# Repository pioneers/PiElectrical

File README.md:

# PiElectrical

This is the working repo for PiElectrical teams

1. [ToDo](#todo)
2. [Repo Structure](#repo-structure)
3. [Setup](#setup)
4. [Work Flow](#work-flow)
5. [How to Create a Gerber](#how-to-create-a-gerber)
6. [Docu Packets](#docu-packets)
7. [FAQ](#faq)
8. [Useful Links](#useful-links)
9. [Standards](#standards)

## ToDo:
* The stuff in PDB-Y16
* Convert motor controller design to KiCad
* Add and test current regulation for motor controller
* Talk to runtime and potentially use cheaper MCU for motor controller

[Back to Top](#pielectrical)

## Repo Structure:

**Boards**: Contains all necessary information about each board, including KiCad (and old Eagle) files, arduino test files, and board specific documentation.

**Bootloaders**: Contains the files necessary to burn the bootloader for boards identifying as Leonardo (Atmega32u4).

**Documentation**: All docu packets and scripts. *Fragile! Do not touch!*

**Production_Files**: Finalized gerbs and other necessary production files (BOM, CPL, etc...) sent out for fabrication.

**Images**: Place all your images in here to enhance your READMEs.

**Libraries**: Necessary KiCad files to work on PiElectrical

ToDo is on the README to keep things easier to see at first glance. GitHub issues tracker can be used as well.

[Back to Top](#pielectrical)

## Setup

<details>
    <summary>When you see an arrow like this... (click me)</summary>
        ...it indicates an expandable section. We usually include images in here as a better reference for you to follow along.
</details>

### Initial Setup of PiElectrical repo on your computer

1. Copy the URL for pioneers/PiElectrical to your clipboard: (Or here: https://github.com/pioneers/PiElectrical.git)
2. In Terminal (Mac, GNU/Linux) or Git Bash (windows), navigate to your working directory (the directory that you want to keep PiElectrical in.)
3. Clone PiElectrical by running this command: `git clone https://github.com/pioneers/PiElectrical.git`

### Installation of KiCad on your computer
1. Download the latest version of KiCad here: https://www.kicad.org/download/
2. <details>
    <summary>Run installer. Use all default settings on installer. (Click to see default settings)<br></summary>
    
</details>

### Setting up KiCad
1. Open KiCad.
2. <details>
    <summary>Depending on whether you've used KiCad before, select the appropriate option on the pop-up. (Default settings if you're new to KiCad).</summary>
    
   </details>

#### Adding Symbols
1. <details>
    <summary>Go to the <i>Preferences</i> tab, and select <i>Manage Symbol Libraries...</i></summary>
    
   </details>
2. <details>
    <summary>If this is your first time using KiCad, it will prompt you to configure the <i>Global Symbol Library</i>. It is highly recommended that you select "Copy default global symbol library table".</summary>
    
   </details>
3. <details>
    <summary>Select the folder icon near the bottom left and navigate to the <i>PiE_Symbols.kicad_sym</i> file in the <i>src</i> folder.</summary>
    
   </details>
4. <details>
    <summary>You should now see the <i>PiE_Symbols</i> in your Symbol Libraries. Make sure the "active" box is checked, and click "OK".</summary>
    
   </details>

#### Adding Footprints
1. <details>
    <summary>Go to the <i>Preferences</i> tab, and select <i>Manage Footprint Libraries...</i></summary>
    
   </details>
2. <details>
    <summary>If this is your first time using KiCad, it will prompt you to configure the <i>Global Footprint Library</i>. It is highly recommended that you select "Copy default global footprint library table".</summary>
    
   </details>
3. <details>
    <summary>Select the folder icon near the bottom left and navigate to the <i>PiE_Footprints.pretty</i> file in the <i>src</i> folder.</summary>
    
   </details>
4. <details>
    <summary>You should now see the <i>PiE_Footprints</i> in your Footprint Libraries. Make sure the "active" box is checked, and click "OK".</summary>
    
   </details>

Note that this setup instruction is based on KiCad 7.0.7, but it should still work for other versions.

[Back to Top](#pielectrical)

## Work Flow

Protocol when working on KiCad files

The revision number should be *REV \<year\>\<revision\>*. E.g. **REV 16A** for year 16 revision A.

If you are not quite familiar with git, see [Useful Links](#useful-links) for the PiE Github tutorial

**WARNING**: Do not modify PiE_Symbols.kicad_sym or PiE_Footprints.pretty without discussing it with PMs.

### Steps when working on KiCad files:

1. In Terminal (mac, GNU/Linux) or GitBash (windows), navigate to your working directory (wherever you have PiElectrical).
2. Make sure your working directory is clean: git status
3. If you haven't started your sub project: git checkout -b YOURNAME-SUBPROJECT
  3. YOUR\_NAME/SUBPROJECT is now the name of your branch
4. Do your work in KiCad.
5. Once you are at a good stopping point in your KiCad work, commit your progress:
    1. git add path/to/your/file
    2. git commit -m "Make your commit message short and with this format"
    3. **NOTE**: Commiting is like saving your file, but for all of PiE as well as your personal computer. And just like saving, Commit Early & Commit Often!
6. Repeat Steps 5 and 6 until you are finished with your EAGLE work.
7. Once you have made your last commit, push your files to the PiElectrical github repo: git push origin YOUR\_BRANCH
    - If you get a merge conflict, contact the PMs for help.
8. If **completely** done, submit a Pull Request

### Commit Message Format Conventions

* Present Tense ("Reroute power traces on team flag", not "Rerouted power traces on team flag")
* No period at the end: ("Reroute power traces on team flag", not "Reroute power traces on team flag.")
* Keep your message length to about one sentence.

### Merge Conflicts: What should I do?

Don't try to fix it yourself: Eagle files are finicky and you might break all your work!

Ask someone who knows how to deal with this, i.e. your PM or something

[Back to Top](#pielectrical)

## Generating Fabrication Outputs

1. Make sure you run the Electrical Rules Check (ERC) in the schematic and the Design Rules Checker (DRC) in the layout, and have no *red* errors. Feel free to ask PMs if you have any questions.
2. <details>
    <summary>Go to File -> Fabrication Outputs -> Gerbers (.gbr)...</summary>
    
   </details>
3. <details>
    <summary>If this is your first time using KiCad, it will prompt you to configure the <i>Global Symbol Library</i>. It is highly recommended that you select "Copy default global symbol library table".</summary>
    
   </details>
4. <details>
    <summary>Select the folder icon near the bottom left and navigate to the <i>PiE_Symbols.kicad_sym</i> file in the <i>src</i> folder.</summary>
    
   </details>
5. <details>
    <summary>You should now see the <i>PiE_Symbols</i> in your Symbol Libraries. Make sure the "active" box is checked, and click "OK".</summary>
    
   </details>

1. Open the brd file
2. Click Cam Job
3. Open pie.cam
4. Make a directory in each sensor's folder called SENSOR\_NAME-gerb
    * SENSOR\_NAME **must** be the exact name as the brd file
5. Run job, and click yes to all for the polygon issue
6. Once all the jobs are done, run `make gerb`

[Back to Top](#pielectrical)

## FAQ

Q: What's the difference between commit before I pull?

A: Do you want to keep any of the changes? Then commit those (the ones you want to keep) before you pull. Or else, the things you pull might conflict with your work, and you'll have a git disaster.

Q: I worked on my stuff, pulled, and everything I did went away!

A: As long as you committed, the PMs can recover your work for you.

Q: Why am I working on my own branch?

A: This is to keep track of pull request and board reviews on a per board basis

[Back to Top](#pielectrical)

## Useful Links

PiE's own [Github Tutorial](https://docs.google.com/a/pioneers.berkeley.edu/presentation/d/1ef5zSDMbE7dCu4XAC4dXhSV5iUd7gjCyXPjRrRvtbQI/edit?usp=sharing)

[PiElectrical Wiki](https://github.com/pioneers/PiElectrical/wiki)

[Markdown Cheatsheet](https://github.com/adam-p/markdown-here/wiki/Markdown-Cheatsheet)

[Arduino Pro Micro Pinouts](https://cdn.sparkfun.com/assets/9/c/3/c/4/523a1765757b7f5c6e8b4567.png)

[BAC DFM](http://instantdfm.bayareacircuits.com/)

Read up on the [PiE Electrical Style Rules and Guidelines](https://staff.pierobotics.org/wiki/Electrical_style_guidelines) (This is a good resource, but outdated)

[Back to Top](#pielectrical)

## Design Rules

You can find JLC's design rules here: https://jlcpcb.com/capabilities/pcb-capabilities. Please review this before ordering a PCB.

#### Some of our general rules:
- Traces **must** be multiples of 45 degrees
- Standard Pin Distance: 100 mils (2.54 mm)

#### Make sure to annotate your boards:

```
Copyright (c) 2023, Pioneers in Engineering
All rights reserved.

Design by: Justin H
This design is open source hardware.
For more information, visit 
github.com/pioneers/PiElectrical
```

[Back to Top](#pielectrical)

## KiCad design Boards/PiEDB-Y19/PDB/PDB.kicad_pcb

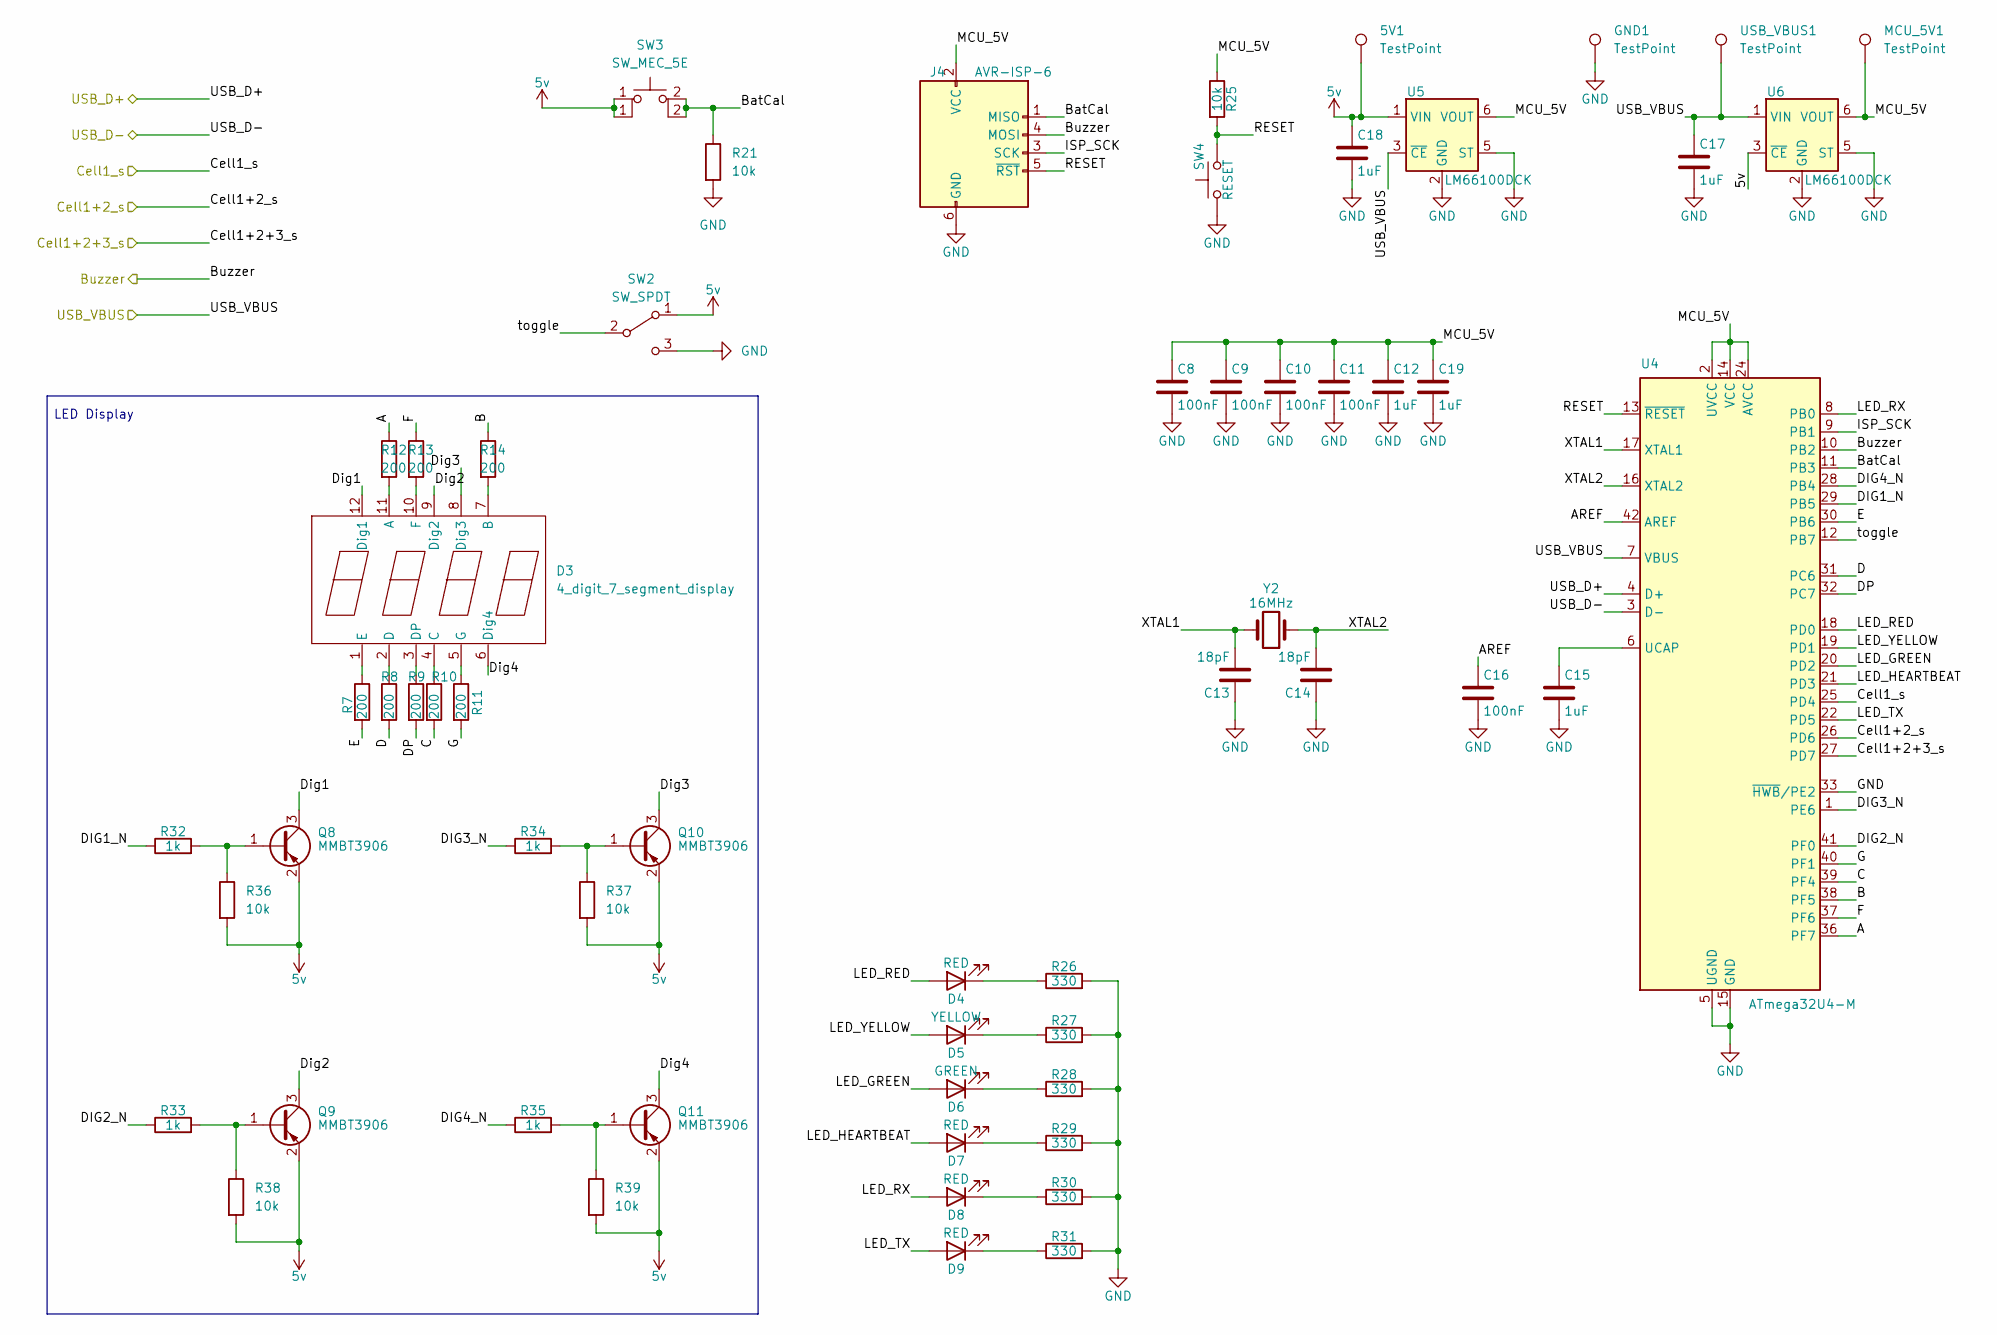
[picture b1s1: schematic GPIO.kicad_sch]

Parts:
5V1: TestPoint; TestPoint_Loop_D2.60mm_Drill0.9mm_Beaded
C8, C9, C10, C11, C16: 100nF; C_0603_1608Metric
C12, C15, C17, C18, C19: 1uF; C_0603_1608Metric
C13, C14: 18pF; C_0603_1608Metric
D3: 4_digit_7_segment_display; LED-SEG-TH_12P-L30.0-W13.7-P2.54-S10.16-BL
D4, D7, D8, D9: RED; LED_0805_2012Metric
D5: YELLOW; LED_0805_2012Metric
D6: GREEN; LED_0805_2012Metric
GND1: TestPoint; TestPoint_Loop_D2.60mm_Drill0.9mm_Beaded
J4: AVR-ISP-6; PinHeader_2x03_P2.54mm_Vertical
MCU_5V1: TestPoint; TestPoint_Loop_D2.60mm_Drill0.9mm_Beaded
Q8, Q9, Q10, Q11: MMBT3906; SOT-23
R7, R8, R9, R10, R11, R12, R13, R14: 200; R_0603_1608Metric
R21, R36, R37, R38, R39: 10k; R_0402_1005Metric
R25: 10k; R_0603_1608Metric
R26, R27, R28, R29, R30, R31: 330; R_0603_1608Metric
R32, R33, R34, R35: 1k; R_0603_1608Metric
SW2: SW_SPDT; DEALON SS-12D01-G3
SW3: SW_MEC_5E; SW_PUSH_6mm
SW4: RESET; SW_PUSH_6mm
U4: ATmega32U4-M; QFN-44-1EP_7x7mm_P0.5mm_EP5.2x5.2mm
U5, U6: LM66100DCK; SOT-363_SC-70-6
USB_VBUS1: TestPoint; TestPoint_Loop_D2.60mm_Drill0.9mm_Beaded
Y2: 16MHz; Crystal_SMD_5032-2Pin_5.0x3.2mm

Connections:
5v: 5V1.1 (1_1), C18.1, Q8.2 (E), Q9.2 (E), Q10.2 (E), Q11.2 (E), R36.2, R37.2, R38.2, R39.2, SW2.1 (A), SW3.1, U5.1 (VIN), U6.3 (~CE); also elsewhere on the board
/Buzzer: J4.4 (MOSI), U4.10 (PB2); also elsewhere on the board
/Cell1+2+3_s: U4.27 (PD7); also elsewhere on the board
/Cell1+2_s: U4.26 (PD6); also elsewhere on the board
/Cell1_s: U4.25 (PD4); also elsewhere on the board
/GPIO/A: R12.1, U4.36 (PF7)
/GPIO/AREF: C16.1, U4.42 (AREF)
/GPIO/B: R14.1, U4.38 (PF5)
/GPIO/BatCal: J4.1 (MISO), R21.1, SW3.2 (A), U4.11 (PB3)
/GPIO/C: R10.2, U4.39 (PF4)
/GPIO/D: R8.2, U4.31 (PC6)
/GPIO/DIG1_N: R32.1, U4.29 (PB5)
/GPIO/DIG2_N: R33.1, U4.41 (PF0)
/GPIO/DIG3_N: R34.1, U4.1 (PE6)
/GPIO/DIG4_N: R35.1, U4.28 (PB4)
/GPIO/DP: R9.2, U4.32 (PC7)
/GPIO/Dig1: D3.12 (Dig1), Q8.3 (C)
/GPIO/Dig2: D3.9 (Dig2), Q9.3 (C)
/GPIO/Dig3: D3.8 (Dig3), Q10.3 (C)
/GPIO/Dig4: D3.6 (Dig4), Q11.3 (C)
/GPIO/E: R7.2, U4.30 (PB6)
/GPIO/F: R13.1, U4.37 (PF6)
/GPIO/G: R11.2, U4.40 (PF1)
/GPIO/ISP_SCK: J4.3 (SCK), U4.9 (PB1)
/GPIO/LED_GREEN: D6.2 (A), U4.20 (PD2)
/GPIO/LED_HEARTBEAT: D7.2 (A), U4.21 (PD3)
/GPIO/LED_RED: D4.2 (A), U4.18 (PD0)
/GPIO/LED_RX: D8.2 (A), U4.8 (PB0)
/GPIO/LED_TX: D9.2 (A), U4.22 (PD5)
/GPIO/LED_YELLOW: D5.2 (A), U4.19 (PD1)
/GPIO/MCU_5V: C8.1, C9.1, C10.1, C11.1, C12.1, C19.1, J4.2 (VCC), MCU_5V1.1 (1_1), R25.1, U4.2 (UVCC), U4.14 (VCC), U4.24 (AVCC), U4.34 (VCC), U4.44 (AVCC), U5.6 (VOUT), U6.6 (VOUT)
/GPIO/RESET: J4.5 (~RST), R25.2, SW4.2, U4.13 (~RESET)
/GPIO/USB_D+: U4.4 (D+); also elsewhere on the board
/GPIO/USB_D-: U4.3 (D-); also elsewhere on the board
/GPIO/USB_VBUS: C17.1, U4.7 (VBUS), U5.3 (~CE), U6.1 (VIN), USB_VBUS1.1 (1_1); also elsewhere on the board
/GPIO/XTAL1: C13.2, U4.17 (XTAL1), Y2.2
/GPIO/XTAL2: C14.2, U4.16 (XTAL2), Y2.1
/GPIO/toggle: SW2.2 (B), U4.12 (PB7)
GND: C8.2, C9.2, C10.2, C11.2, C12.2, C13.1, C14.1, C15.2, C16.2, C17.2, C18.2, C19.2, GND1.1 (1_1), J4.6 (GND), R21.2, R26.2, R27.2, R28.2, R29.2, R30.2, R31.2, SW2.3 (C), SW4.1, U4.5 (UGND), U4.15 (GND), U4.23 (GND), U4.33 (~HWB/PE2), U4.35 (GND), U4.43 (GND), U4.45 (GND), U5.2 (GND), U5.5 (ST), U6.2 (GND), U6.5 (ST); also elsewhere on the board
unnamed: D3.11 (A), R12.2
unnamed: D3.7 (B), R14.2
unnamed: D3.4 (C), R10.1
unnamed: D3.2 (D), R8.1
unnamed: D3.3 (DP), R9.1
unnamed: D3.1 (E), R7.1
unnamed: D3.10 (F), R13.2
unnamed: D3.5 (G), R11.1
unnamed: D4.1 (K), R26.1
unnamed: D5.1 (K), R27.1
unnamed: D6.1 (K), R28.1
unnamed: D7.1 (K), R29.1
unnamed: D8.1 (K), R30.1
unnamed: D9.1 (K), R31.1
unnamed: Q8.1 (B), R32.2, R36.1
unnamed: Q9.1 (B), R33.2, R38.1
unnamed: Q10.1 (B), R34.2, R37.1
unnamed: Q11.1 (B), R35.2, R39.1
unnamed: C15.1, U4.6 (UCAP)

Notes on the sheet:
LED Display

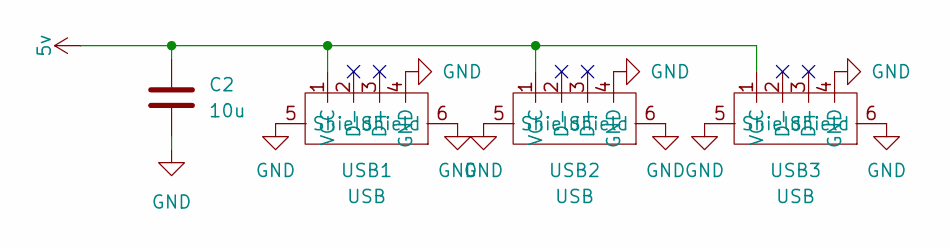
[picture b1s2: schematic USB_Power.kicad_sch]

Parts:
C2: 10u; CP_Radial_D5.0mm_P2.00mm
USB1, USB2, USB3: USB; USB-A_female

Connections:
5v: C2.1, USB1.1 (VCC), USB2.1 (VCC), USB3.1 (VCC); also elsewhere on the board
GND: C2.2, USB1.4 (GND), USB1.5 (Shield), USB1.6 (Shield), USB2.4 (GND), USB2.5 (Shield), USB2.6 (Shield), USB3.4 (GND), USB3.5 (Shield), USB3.6 (Shield); also elsewhere on the board

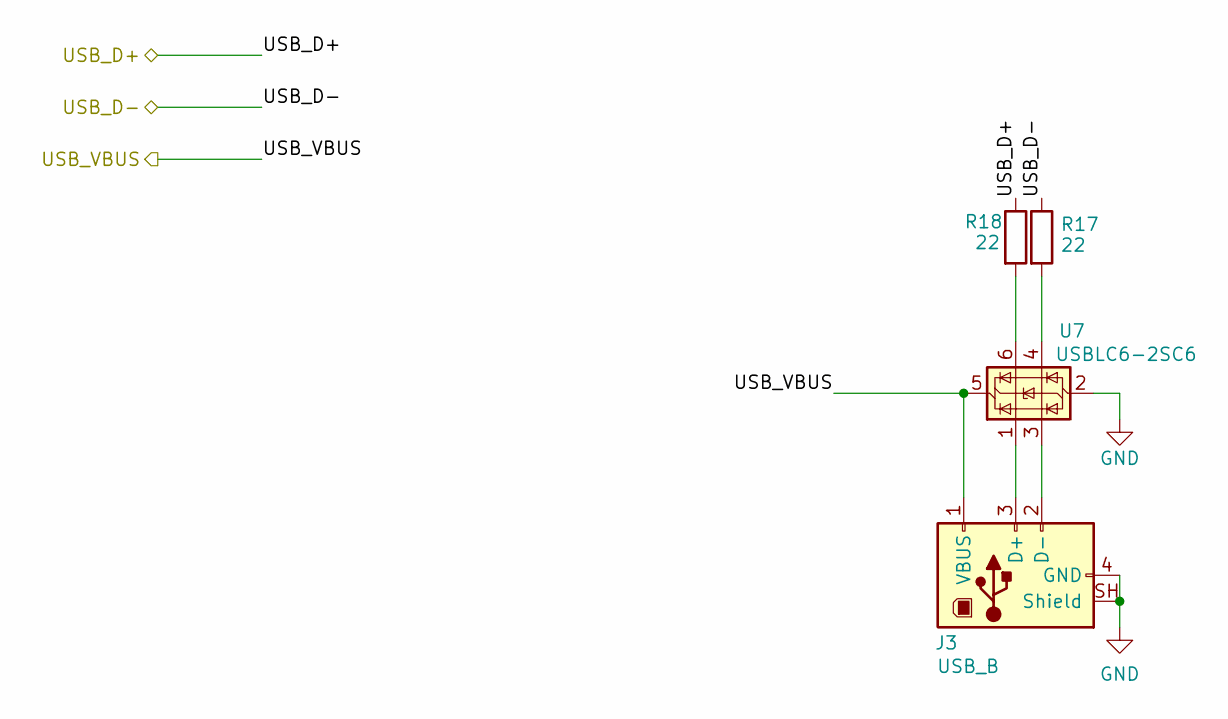
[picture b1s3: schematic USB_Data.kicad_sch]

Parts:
J3: USB_B; USB_B_OST_USB-B1HSxx_Horizontal
R17, R18: 22; R_0603_1608Metric
U7: USBLC6-2SC6; SOT-23-6

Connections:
/GPIO/USB_D+: R18.1; also elsewhere on the board
/GPIO/USB_D-: R17.1; also elsewhere on the board
/GPIO/USB_VBUS: J3.1 (VBUS), U7.5 (VBUS); also elsewhere on the board
GND: J3.4 (GND), J3.SH (Shield), U7.2 (GND); also elsewhere on the board
unnamed: J3.3 (D+), U7.1 (I/O1)
unnamed: J3.2 (D-), U7.3 (I/O2)
unnamed: R17.2, U7.4 (I/O2)
unnamed: R18.2, U7.6 (I/O1)

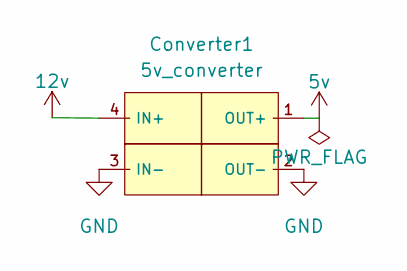
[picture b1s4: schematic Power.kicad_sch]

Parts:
Converter1: 5v_converter

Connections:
5v: Converter1.1 (OUT+); also elsewhere on the board
12v: Converter1.4 (IN+); also elsewhere on the board
GND: Converter1.2 (OUT-), Converter1.3 (IN-); also elsewhere on the board

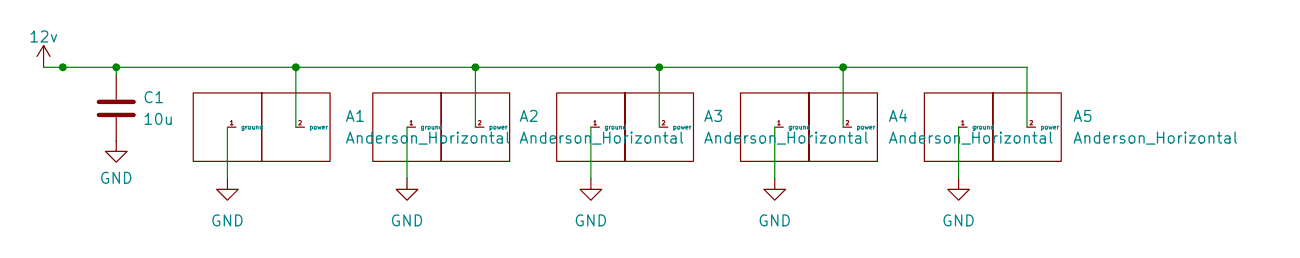
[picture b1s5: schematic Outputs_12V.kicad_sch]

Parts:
A1, A2, A3, A4, A5: Anderson_Horizontal; anderson_horizontal
C1: 10u; CP_Radial_D5.0mm_P2.00mm

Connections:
12v: A1.2 (power), A2.2 (power), A3.2 (power), A4.2 (power), A5.2 (power), C1.1; also elsewhere on the board
GND: A1.1 (ground), A2.1 (ground), A3.1 (ground), A4.1 (ground), A5.1 (ground), C1.2; also elsewhere on the board

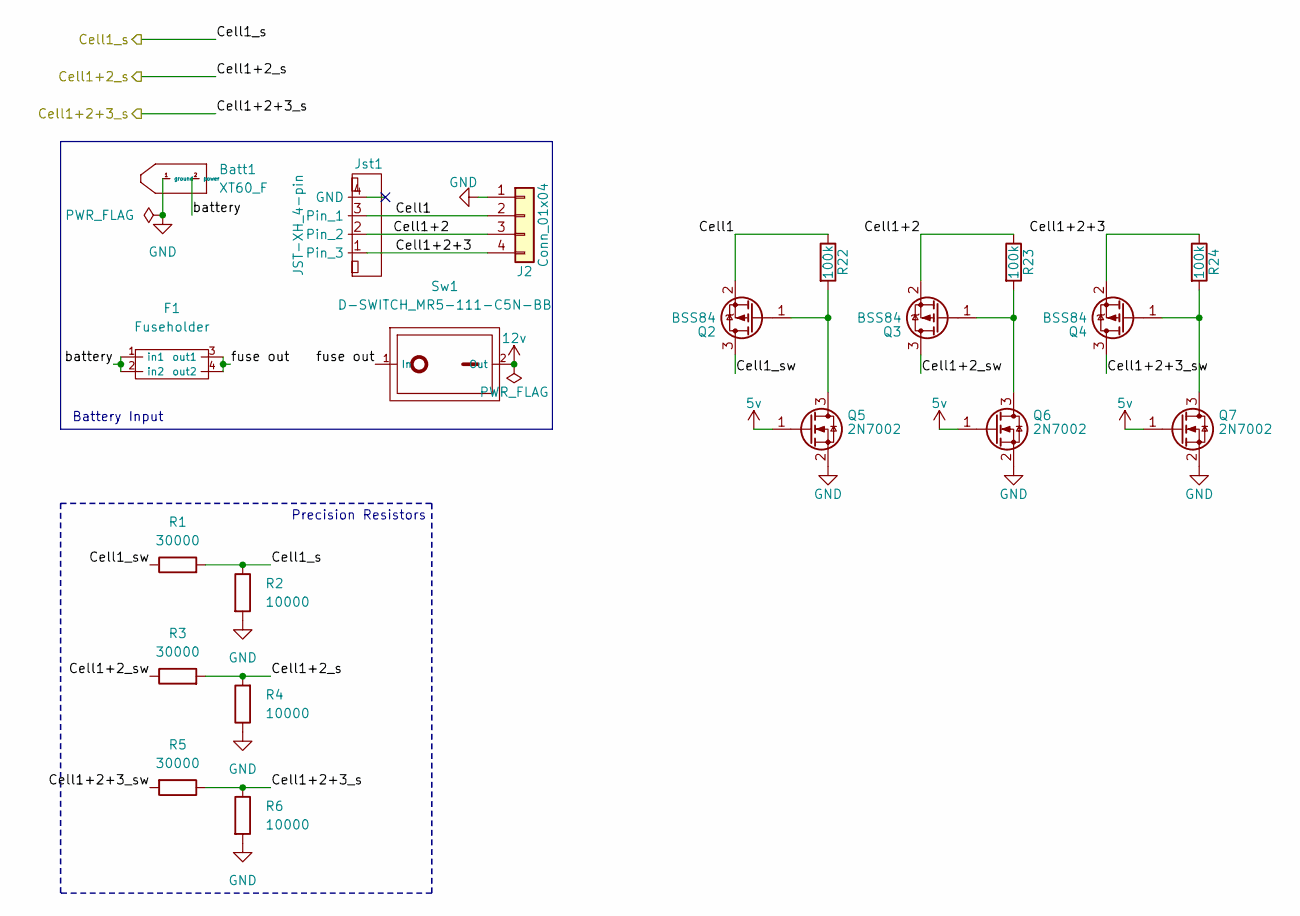
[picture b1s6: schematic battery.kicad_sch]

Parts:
Batt1: XT60_F; AMASS_XT60-M_1x02_P7.20mm_Vertical
F1: Fuseholder; Fuse Holder SMD
J2: Conn_01x04; PinHeader_1x04_P2.54mm_Vertical
Jst1: JST-XH_4-pin; JST_XH_B4B-XH-A_1x04_P2.50mm_Vertical
Q2, Q3, Q4: BSS84; SOT-23
Q5, Q6, Q7: 2N7002; SOT-23
R1, R3, R5: 30000; R_0603_1608Metric
R2, R4, R6: 10000; R_0603_1608Metric
R22, R23, R24: 100k; R_0603_1608Metric
Sw1: D-SWITCH_MR5-111-C5N-BB; Rocker Switch

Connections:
5v: Q5.1 (G), Q6.1 (G), Q7.1 (G); also elsewhere on the board
12v: Sw1.2 (Out); also elsewhere on the board
/Battery/Cell1: J2.2, Jst1.3 (Pin_1), Q2.2 (S), R22.1
/Battery/Cell1+2: J2.3, Jst1.2, Q3.2 (S), R23.1
/Battery/Cell1+2+3: J2.4, Jst1.1 (Pin_3), Q4.2 (S), R24.1
/Battery/Cell1+2+3_sw: Q4.3 (D), R5.2
/Battery/Cell1+2_sw: Q3.3 (D), R3.1
/Battery/Cell1_sw: Q2.3 (D), R1.1
/Battery/battery: Batt1.2 (power), F1.1 (in1), F1.2 (in2)
/Battery/fuse out: F1.3 (out1), F1.4 (out2), Sw1.1 (In)
/Cell1+2+3_s: R5.1, R6.1; also elsewhere on the board
/Cell1+2_s: R3.2, R4.2; also elsewhere on the board
/Cell1_s: R1.2, R2.1; also elsewhere on the board
GND: Batt1.1 (ground), J2.1, Q5.2 (S), Q6.2 (S), Q7.2 (S), R2.2, R4.1, R6.2; also elsewhere on the board
unnamed: Q2.1 (G), Q5.3 (D), R22.2
unnamed: Q3.1 (G), Q6.3 (D), R23.2
unnamed: Q4.1 (G), Q7.3 (D), R24.2

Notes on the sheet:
Precision Resistors
Battery Input

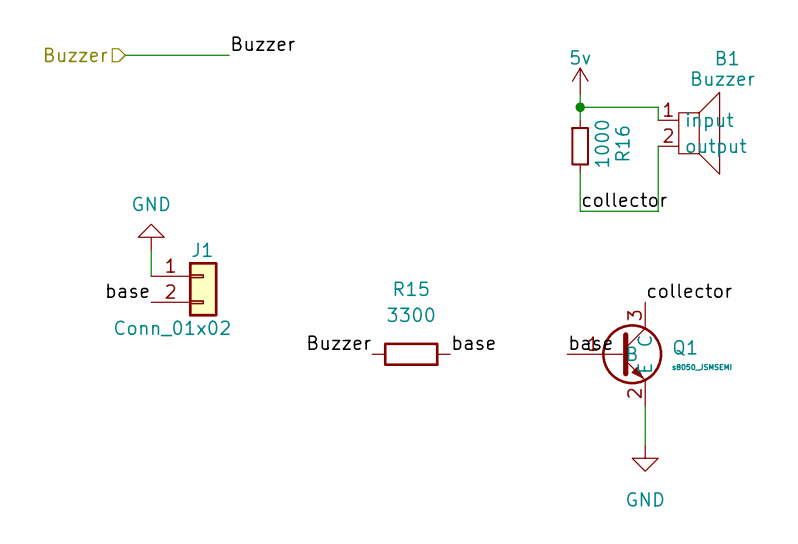
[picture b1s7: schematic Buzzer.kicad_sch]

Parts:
B1: Buzzer
J1: Conn_01x02; PinHeader_1x02_P2.54mm_Vertical
Q1: s8050_JSMSEMI; s8050 JSMSEMI
R15: 3300; R_0603_1608Metric
R16: 1000; R_0603_1608Metric

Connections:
5v: B1.1 (input), R16.1; also elsewhere on the board
/Buzzer: R15.1; also elsewhere on the board
/Buzzer/base: J1.2, Q1.1 (B), R15.2
/Buzzer/collector: B1.2 (output), Q1.3 (C), R16.2
GND: J1.1, Q1.2 (E); also elsewhere on the board

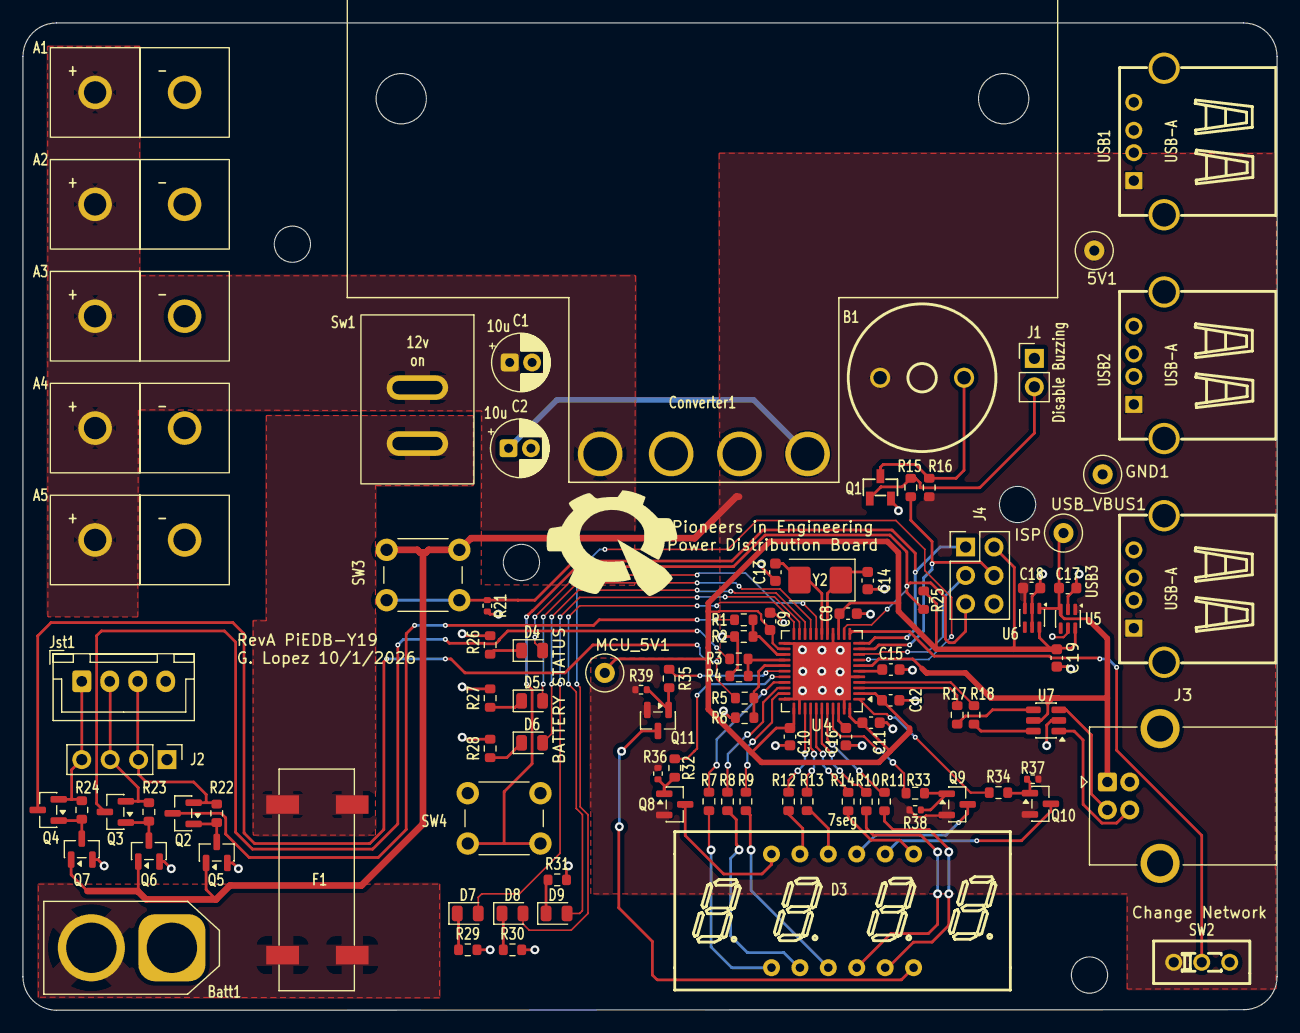
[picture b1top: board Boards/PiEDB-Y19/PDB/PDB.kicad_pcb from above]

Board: 2 copper layers, 112.1 x 88.2 mm, 99 parts (0 on the bottom side), 76 nets.

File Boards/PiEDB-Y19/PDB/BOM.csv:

"Id";"Designator";"Footprint";"Quantity";"Designation";"Supplier and ref";
1;"5V1, GND1, MCU_5V1, USB_VBUS1";"TestPoint_Loop_D2.60mm_Drill0.9mm_Beaded";4;"TestPoint";;;
2;"A1, A2, A3, A4, A5";"anderson_horizontal";5;"Anderson_Horizontal";;;
3;"B1";"Buzzer";1;"Buzzer";;;
4;"Batt1";"AMASS_XT60-M_1x02_P7.20mm_Vertical";1;"XT60_F";;;
5;"C1, C2";"CP_Radial_D5.0mm_P2.00mm";2;"10u";;;
6;"C8, C9, C10, C11, C16";"C_0603_1608Metric";5;"100nF";;;
7;"C12, C15, C17, C18, C19";"C_0603_1608Metric";5;"1uF";;;
8;"C13, C14";"C_0603_1608Metric";2;"18pF";;;
9;"Converter1";"5v_converter";1;"5v_converter";;;
10;"D3";"LED-SEG-TH_12P-L30.0-W13.7-P2.54-S10.16-BL";1;"4_digit_7_segment_display";;;
11;"D4, D7, D8, D9";"LED_0805_2012Metric";4;"RED";;;
12;"D5";"LED_0805_2012Metric";1;"YELLOW";;;
13;"D6";"LED_0805_2012Metric";1;"GREEN";;;
14;"F1";"Fuse Holder SMD";1;"Fuseholder";;;
15;"J1";"PinHeader_1x02_P2.54mm_Vertical";1;"Conn_01x02";;;
16;"J2";"PinHeader_1x04_P2.54mm_Vertical";1;"Conn_01x04";;;
17;"J3";"USB_B_OST_USB-B1HSxx_Horizontal";1;"USB_B";;;
18;"J4";"PinHeader_2x03_P2.54mm_Vertical";1;"AVR-ISP-6";;;
19;"Jst1";"JST_XH_B4B-XH-A_1x04_P2.50mm_Vertical";1;"JST-XH_4-pin";;;
20;"Q1";"s8050 JSMSEMI";1;"s8050_JSMSEMI";;;
21;"Q2, Q3, Q4";"SOT-23";3;"BSS84";;;
22;"Q5, Q6, Q7";"SOT-23";3;"2N7002";;;
23;"Q8, Q9, Q10, Q11";"SOT-23";4;"MMBT3906";;;
24;"R1, R3, R5";"R_0603_1608Metric";3;"30000";;;
25;"R2, R4, R6";"R_0603_1608Metric";3;"10000";;;
26;"R7, R8, R9, R10, R11, R12, R13, R14";"R_0603_1608Metric";8;"200";;;
27;"R15";"R_0603_1608Metric";1;"3300";;;
28;"R16";"R_0603_1608Metric";1;"1000";;;
29;"R17, R18";"R_0603_1608Metric";2;"22";;;
30;"R21, R36, R37, R38, R39";"R_0402_1005Metric";5;"10k";;;
31;"R22, R23, R24";"R_0603_1608Metric";3;"100k";;;
32;"R25";"R_0603_1608Metric";1;"10k";;;
33;"R26, R27, R28, R29, R30, R31";"R_0603_1608Metric";6;"330";;;
34;"R32, R33, R34, R35";"R_0603_1608Metric";4;"1k";;;
35;"REF**, REF**, REF**, REF**";"Hole_R1.62mm";4;"Hole_R1.62mm";;;
36;"Sw1";"Rocker Switch";1;"D-SWITCH_MR5-111-C5N-BB";;;
37;"SW2";"DEALON SS-12D01-G3";1;"SW_SPDT";;;
38;"SW3";"SW_PUSH_6mm";1;"SW_MEC_5E";;;
39;"SW4";"SW_PUSH_6mm";1;"RESET";;;
40;"U4";"QFN-44-1EP_7x7mm_P0.5mm_EP5.2x5.2mm";1;"ATmega32U4-M";;;
41;"U5, U6";"SOT-363_SC-70-6";2;"LM66100DCK";;;
42;"U7";"SOT-23-6";1;"USBLC6-2SC6";;;
43;"USB1, USB2, USB3";"USB-A_female";3;"USB";;;
44;"Y2";"Crystal_SMD_5032-2Pin_5.0x3.2mm";1;"16MHz";;;

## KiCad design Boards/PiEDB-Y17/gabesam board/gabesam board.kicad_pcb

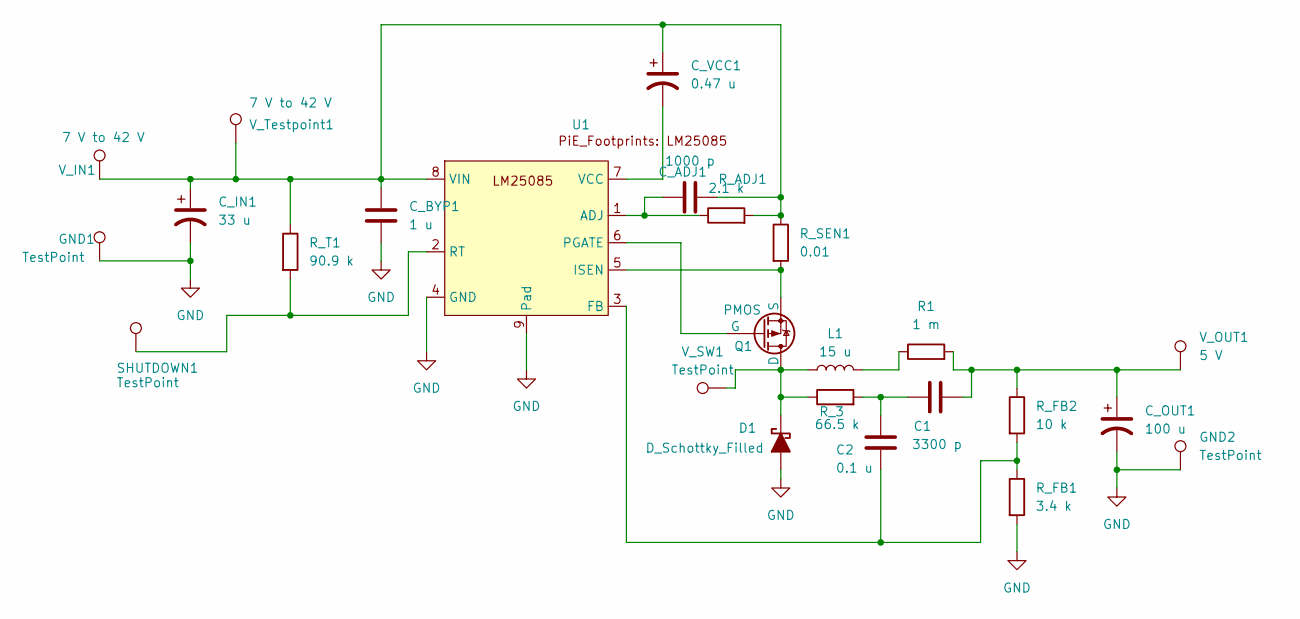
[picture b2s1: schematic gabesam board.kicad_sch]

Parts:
C1: 3300 p; C_1206
C2: 0.1 u; C_1206
C_ADJ1: 1000 p; C_1206
C_BYP1: 1 u; C_1206
C_IN1: 33 u; C_1206
C_OUT1: 100 u; C_1206
C_VCC1: 0.47 u; C_1206
D1: D_Schottky_Filled; D_1206_3216Metric_Pad1.42x1.75mm_HandSolder
GND1, GND2: TestPoint; TestPoint_Loop_D2.60mm_Drill0.9mm_Beaded
L1: 15 u; L_1206_3216Metric
Q1: PMOS; PowerPAK_SO-8_Single
R1: 1 m; R_1206
R_3: 66.5 k; R_1206
R_ADJ1: 2.1 k; R_1206
R_FB1: 3.4 k; R_1206
R_FB2: 10 k; R_1206
R_SEN1: 0.01; R_1206
R_T1: 90.9 k; R_1206
SHUTDOWN1: TestPoint; TestPoint_Loop_D2.60mm_Drill0.9mm_Beaded
U1: LM25085-Q1
V_IN1: 7 V to 42 V; TestPoint_Loop_D2.60mm_Drill0.9mm_Beaded
V_OUT1: 5 V; TestPoint_Loop_D2.60mm_Drill0.9mm_Beaded
V_SW1: TestPoint; TestPoint_Loop_D2.60mm_Drill0.9mm_Beaded
V_Testpoint1: 7 V to 42 V; TestPoint_Loop_D2.60mm_Drill0.9mm_Beaded

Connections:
GND: C_BYP1.2, C_IN1.2, C_OUT1.2, D1.2 (A), GND1.1, GND2.1, R_FB1.2, U1.4 (GND), U1.9 (Pad)
unnamed: C1.1, C2.2, R_3.2
unnamed: C1.2, C_OUT1.1, R1.2, R_FB2.1, V_OUT1.1
unnamed: D1.1 (K), L1.1, Q1.1 (D), R_3.1, V_SW1.1
unnamed: L1.2, R1.1
unnamed: Q1.2 (G), U1.6 (PGATE)
unnamed: Q1.3 (S), R_SEN1.2, U1.5 (ISEN)
unnamed: C_ADJ1.1, R_ADJ1.1, U1.1 (ADJ)
unnamed: C2.1, R_FB1.1, R_FB2.2, U1.3 (FB)
unnamed: R_T1.2, SHUTDOWN1.1, U1.2 (RT)
unnamed: C_VCC1.2, U1.7 (VCC)
unnamed: C_ADJ1.2, C_BYP1.1, C_IN1.1, C_VCC1.1, R_ADJ1.2, R_SEN1.1, R_T1.1, U1.8 (VIN), V_IN1.1, V_Testpoint1.1

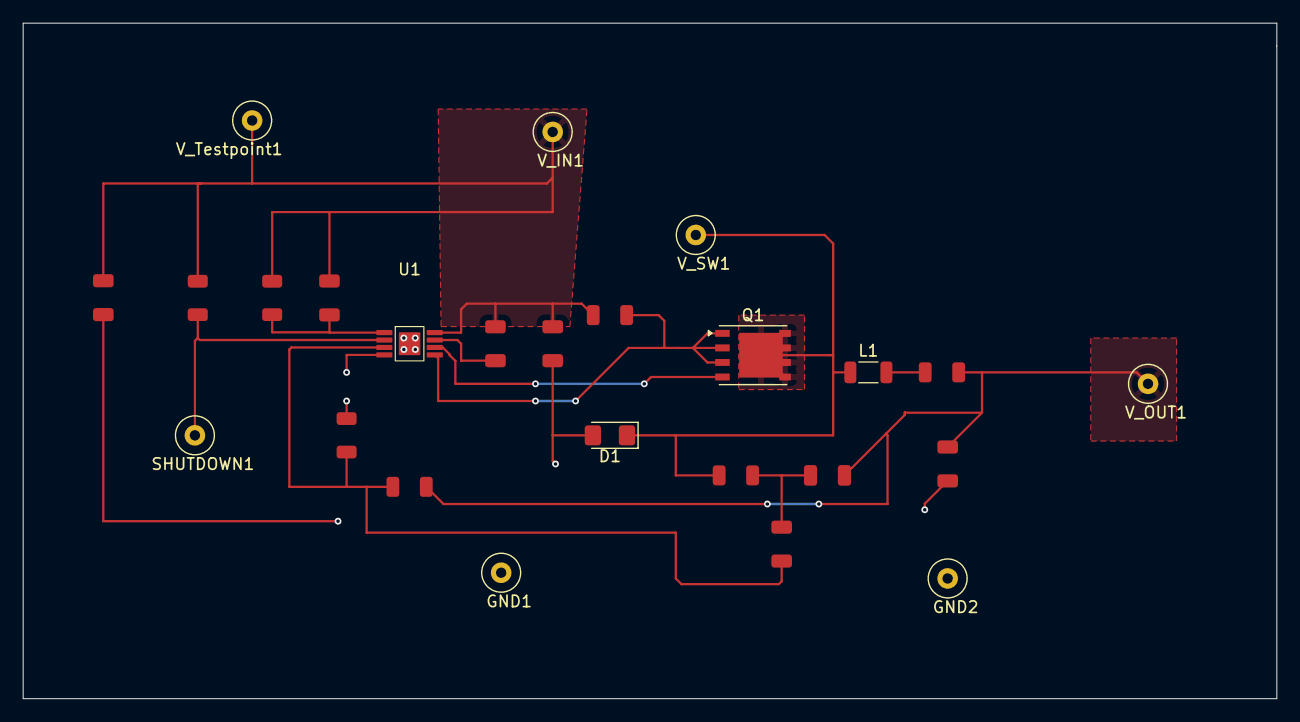
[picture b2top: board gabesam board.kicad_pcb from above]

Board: 2 copper layers, 109.5 x 59.0 mm, 25 parts (0 on the bottom side), 12 nets.

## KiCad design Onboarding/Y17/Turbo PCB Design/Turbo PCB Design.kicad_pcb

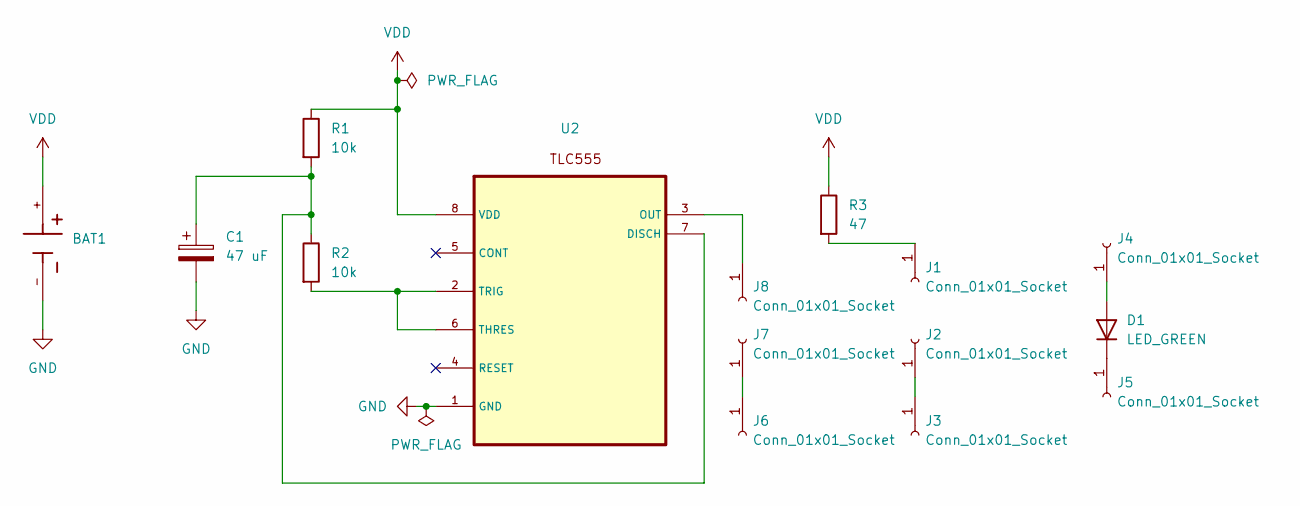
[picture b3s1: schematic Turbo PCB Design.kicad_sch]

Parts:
BAT1: BAT_BS-7
C1: 47 uF; CP_Radial_D4.0mm_P1.50mm
D1: LED_GREEN; LED_D5.0mm
J1, J2, J3, J4, J5, J6, J7, J8: Conn_01x01_Socket; MountingHole_1.0mm_M2_Pad
R1, R2: 10k; R_2512_6332Metric_Pad1.40x3.35mm_HandSolder
R3: 47; R_2512_6332Metric_Pad1.40x3.35mm_HandSolder
U2: TLC555_SCHE

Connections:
GND: BAT1.-, C1.2, U2.1 (GND)
unnamed: D1.2 (A), J4.1
unnamed: D1.1 (K), J5.1
unnamed: J1.1, R3.2
unnamed: J2.1, J3.1
unnamed: J6.1, J7.1
unnamed: J8.1, U2.3 (OUT)
unnamed: C1.1, R1.2, R2.1, U2.7 (DISCH)
unnamed: R2.2, U2.2 (TRIG), U2.6 (THRES)
VDD: BAT1.+, R1.1, R3.1, U2.8 (VDD)

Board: 2 copper layers, 15 parts (0 on the bottom side), 10 nets, no tracks yet.

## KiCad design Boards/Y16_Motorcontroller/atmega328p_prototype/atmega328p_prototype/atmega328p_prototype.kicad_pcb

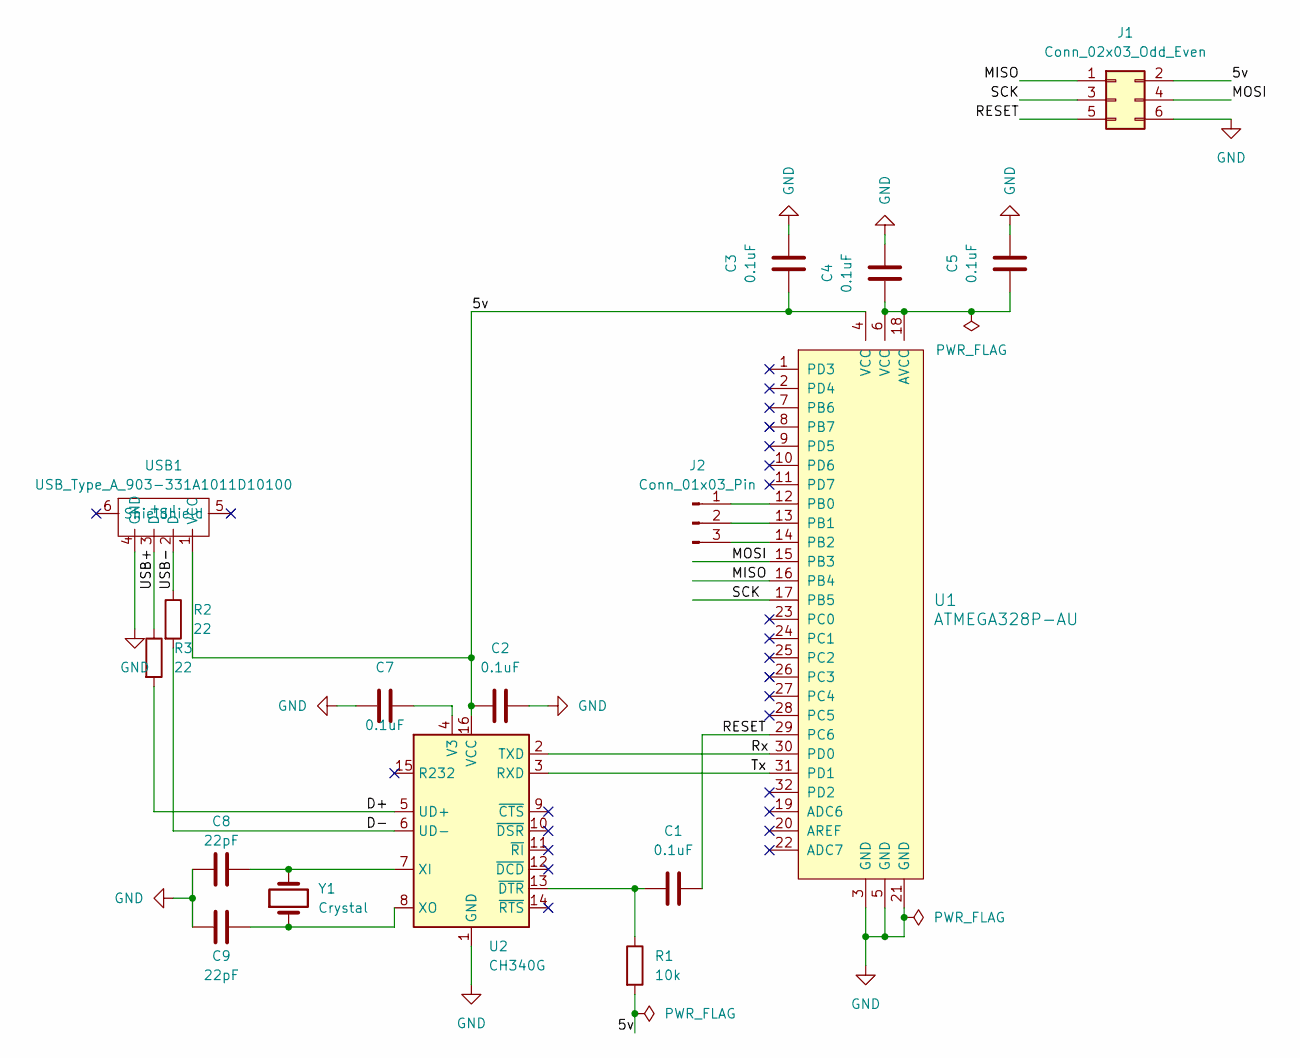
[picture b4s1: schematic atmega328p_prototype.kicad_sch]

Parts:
C1, C2, C3, C4, C5, C7: 0.1uF; C_0603_1608Metric
C8, C9: 22pF; C_0603_1608Metric
J1: Conn_02x03_Odd_Even; PinHeader_2x03_P2.54mm_Vertical
J2: Conn_01x03_Pin; PinHeader_1x03_P2.54mm_Vertical
R1: 10k; R_0603_1608Metric
R2, R3: 22; R_0603_1608Metric
U1: ATMEGA328P-AU; TQFP-32_7x7mm; MPN ATMEGA328P-AU; Digi-Key_PN ATMEGA328P-AU-ND
U2: CH340G; SOIC-16_3.9x9.9mm_P1.27mm
USB1: USB_Type_A_903-331A1011D10100; USB-A_female
Y1: Crystal; JYJE S1C12000VWFAC

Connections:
/5v: C2.1, C3.1, J1.2, R1.2, U1.4 (VCC), U2.16 (VCC), USB1.1 (VCC)
/D+: R3.2, U2.5 (UD+)
/D-: R2.2, U2.6 (UD-)
/MISO: J1.1, U1.16 (PB4)
/MOSI: J1.4, U1.15 (PB3)
/RESET: C1.2, J1.5, U1.29 (PC6)
/Rx: U1.30 (PD0), U2.2 (TXD)
/SCK: J1.3, U1.17 (PB5)
/Tx: U1.31 (PD1), U2.3 (RXD)
/USB+: R3.1, USB1.3 (D+)
/USB-: R2.1, USB1.2 (D-)
GND: C2.2, C3.2, C4.2, C5.2, C7.2, C8.1, C9.2, J1.6, U1.3 (GND), U1.5 (GND), U1.21 (GND), U2.1 (GND), USB1.4 (GND)
unnamed: J2.1, U1.12 (PB0)
unnamed: J2.2, U1.13 (PB1)
unnamed: J2.3, U1.14 (PB2)
unnamed: C4.1, C5.1, U1.6 (VCC), U1.18 (AVCC)
unnamed: C7.1, U2.4 (V3)
unnamed: C8.2, U2.7 (XI), Y1.2
unnamed: C9.1, U2.8 (XO), Y1.1
unnamed: C1.1, R1.1, U2.13 (~DTR)

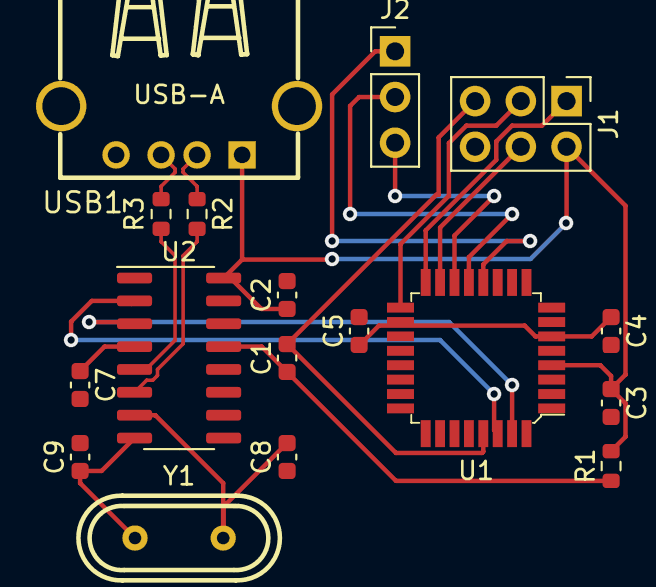
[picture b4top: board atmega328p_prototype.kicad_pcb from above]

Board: 2 copper layers, 17 parts (0 on the bottom side), 20 nets.

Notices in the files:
Boards/PiEDB-Y16/PDB/PDB.kicad_pcb:
Copyright (c) 2024, Pioneers in Engineering
All rights reserved.
Boards/PiEDB-Y19/PDB/PDB.kicad_pcb:
Copyright (c) 2026, Pioneers in Engineering
